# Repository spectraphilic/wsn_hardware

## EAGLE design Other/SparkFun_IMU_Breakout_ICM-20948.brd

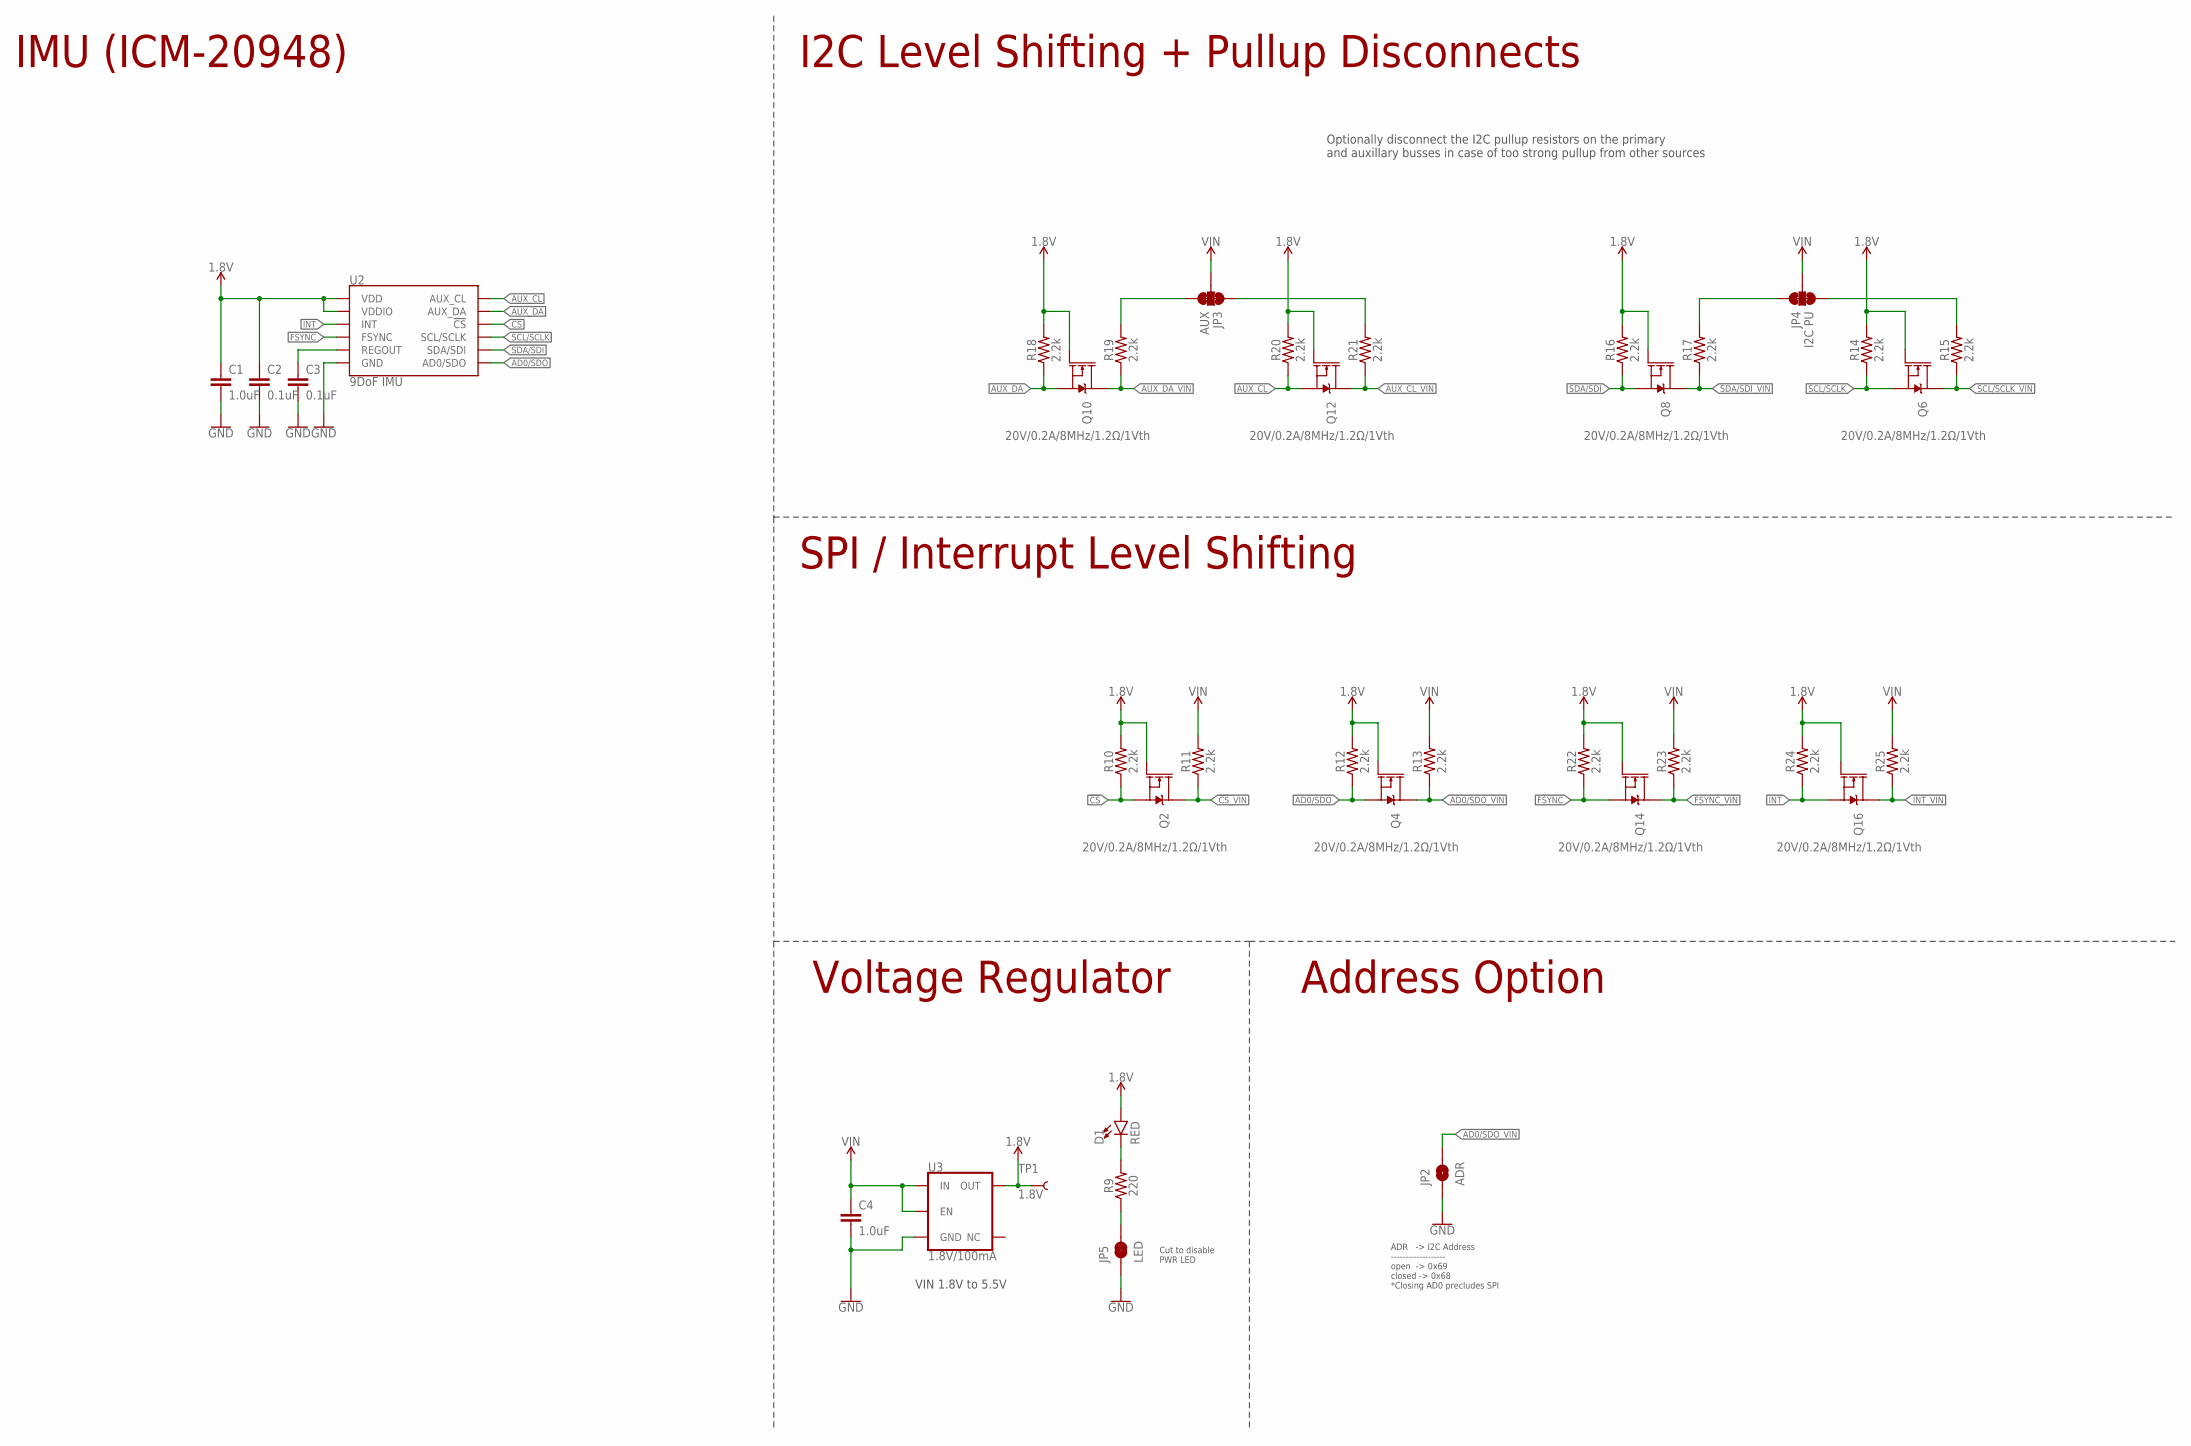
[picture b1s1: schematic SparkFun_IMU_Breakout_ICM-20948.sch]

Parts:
C1, C4: 1.0uF; 0603
C2, C3: 0.1uF; 0603
D1: RED; LED-0603
JP2: ADR; SMT-JUMPER_2_NO_SILK
JP3: AUX; SMT-JUMPER_3_2-NC_TRACE_SILK
JP4: I2C PU; SMT-JUMPER_3_2-NC_TRACE_SILK
JP5: LED; SMT-JUMPER_2_NC_TRACE_SILK
Q2, Q4, Q6, Q8, Q10, Q12, Q14, Q16: 20V/0.2A/8MHz/1.2Ω/1Vth; SOT-416FL
R9: 220; 0603
R10, R11, R12, R13, R14, R15, R16, R17, R18, R19, R20, R21, R22, R23, R24, R25: 2.2k; 0402-TIGHT
TP1: 1.8V; PAD.03X.03
U2: 9DoF IMU; QFN24-3X3
U3: 1.8V/100mA; SC70

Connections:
1.8V: C1.1, C2.1, D1.A, Q2.1 (G), Q4.1 (G), Q6.1 (G), Q8.1 (G), Q10.1 (G), Q12.1 (G), Q14.1 (G), Q16.1 (G), R10.2, R12.2, R14.2, R16.2, R18.2, R20.2, R22.2, R24.2, TP1.P$1, U2.8 (VDDIO), U2.13 (VDD), U3.5 (OUT)
!CS: Q2.2 (S), R10.1, U2.22 (!CS)
!CS!_VIN: Q2.3 (D), R11.1
AD0/SDO: Q4.2 (S), R12.1, U2.9 (AD0/SDO)
AD0/SDO_VIN: JP2.2, Q4.3 (D), R13.1
AUX_CL: Q12.2 (S), R20.1, U2.7 (AUX_CL)
AUX_CL_VIN: Q12.3 (D), R21.1
AUX_DA: Q10.2 (S), R18.1, U2.21 (AUX_DA)
AUX_DA_VIN: Q10.3 (D), R19.1
FSYNC: Q14.2 (S), R22.1, U2.11 (FSYNC)
FSYNC_VIN: Q14.3 (D), R23.1
GND: C1.2, C2.2, C3.2, C4.2, JP2.1, JP5.1, U2.18 (GND), U2.20 (GND), U3.2 (GND)
INT: Q16.2 (S), R24.1, U2.12 (INT)
INT_VIN: Q16.3 (D), R25.1
unnamed: C3.1, U2.10 (REGOUT)
unnamed: JP4.3, R15.2
unnamed: JP4.1, R17.2
unnamed: JP3.1, R21.2
unnamed: JP3.3, R19.2
unnamed: D1.C, R9.2
unnamed: JP5.2, R9.1
SCL/SCLK: Q6.2 (S), R14.1, U2.23 (SCL/SCLK)
SCL/SCLK_VIN: Q6.3 (D), R15.1
SDA/SDI: Q8.2 (S), R16.1, U2.24 (SDA/SDI)
SDA/SDI_VIN: Q8.3 (D), R17.1
VIN: C4.1, JP3.2, JP4.2, R11.2, R13.2, R23.2, R25.2, U3.1 (IN), U3.3 (EN)

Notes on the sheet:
VIN 1.8V to 5.5V
IMU (ICM-20948)
I2C Level Shifting + Pullup Disconnects
Voltage Regulator
SPI / Interrupt Level Shifting
ADR -> I2C Address ------------------- open -> 0x69 closed -> 0x68 *Closing AD0 precludes SPI
Optionally disconnect the I2C pullup resistors on the primary and auxillary busses in case of too strong pullup from other sources
Cut to disable PWR LED
Address Option

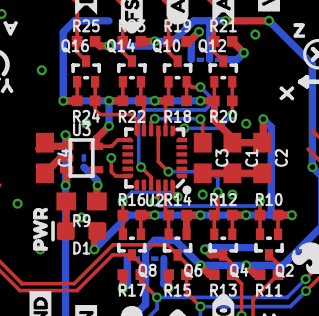
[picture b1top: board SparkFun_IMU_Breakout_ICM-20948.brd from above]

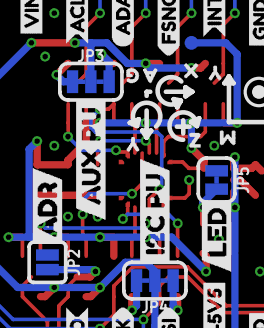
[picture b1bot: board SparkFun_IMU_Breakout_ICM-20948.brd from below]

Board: 2 copper layers, 80 parts (30 on the bottom side), 26 nets.

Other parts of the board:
U$1, U$2, U$22: GND4
U$3: PWR0
U$4, U$21: INT3
U$5, U$20: FSNC2
U$6, U$19: ACL1
U$7, U$18: ADA0
U$8: MISO13
U$9: MOSI14
U$10: SCLK15
U$11: #CS16
U$12: 1V8#5V57
U$13, U$30, U$44: VIN5
U$14: NC17
U$15: CL4
U$16: DA2
U$17: AD012
U$23: ADR2
U$25: I2C_PU21
U$27: AUX_PU24
U$28: SFE_LOGO_FLAME_.1
U$29: LED23
U$35, U$51, U$58: Y1
U$37, U$60: G5
U$38, U$61: A4
U$40, U$50, U$57: X0
U$42, U$59: Z2
U$43: QWIIC_9DOF_IMU_0
U$49: M3

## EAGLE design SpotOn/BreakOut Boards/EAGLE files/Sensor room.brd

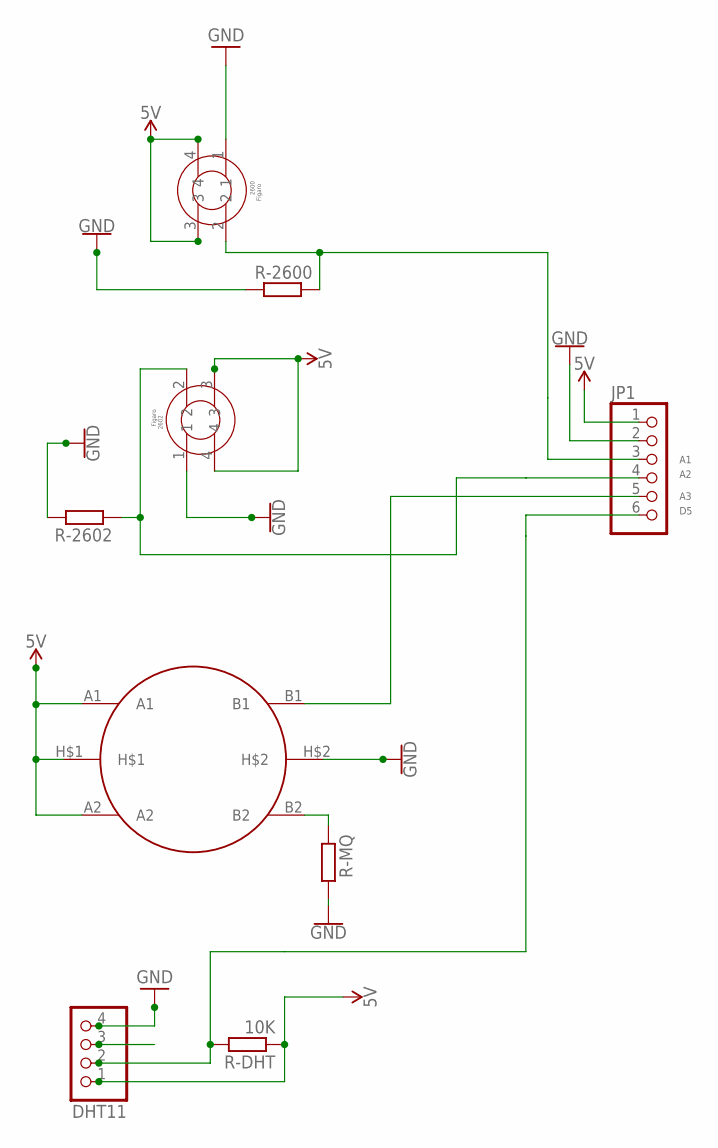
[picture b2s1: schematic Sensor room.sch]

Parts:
2600, 2602: FIGARO2602
DHT11: PINHD-1X4; 1X04
JP1: PINHD-1X6CB; 1X06-CLEANBIG
MQ-135: MQ_135_A; MQ-135
R-2600, R-2602: R0207/10; 0207/10
R-DHT: 10K; 0207/10
R-MQ: R0207/10; 0207/10

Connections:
5V: 2600.3 (4), 2600.4 (3), 2602.3 (4), 2602.4 (3), DHT11.1, JP1.1, MQ-135.A1, MQ-135.A2, MQ-135.H$1, R-DHT.1
GND: 2600.1 (2), 2602.1 (2), DHT11.4, JP1.2, MQ-135.H$2, R-2600.1, R-2602.2, R-MQ.2
unnamed: DHT11.2, JP1.6, R-DHT.2
unnamed: JP1.5, MQ-135.B1
unnamed: MQ-135.B2, R-MQ.1
unnamed: 2602.2 (1), JP1.4, R-2602.1
unnamed: 2600.2 (1), JP1.3, R-2600.2

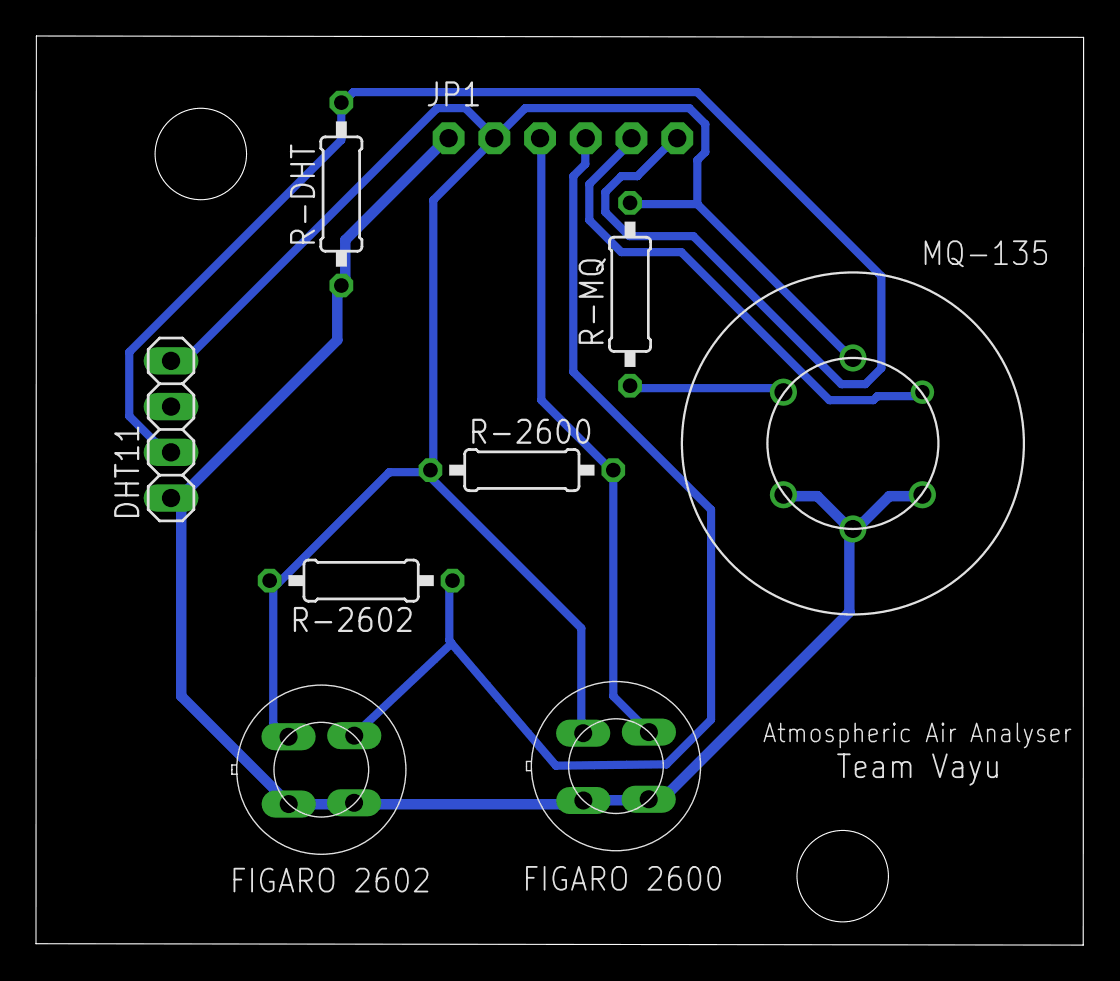
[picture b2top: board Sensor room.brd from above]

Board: 2 copper layers, 58.2 x 50.5 mm, 9 parts (0 on the bottom side), 7 nets.

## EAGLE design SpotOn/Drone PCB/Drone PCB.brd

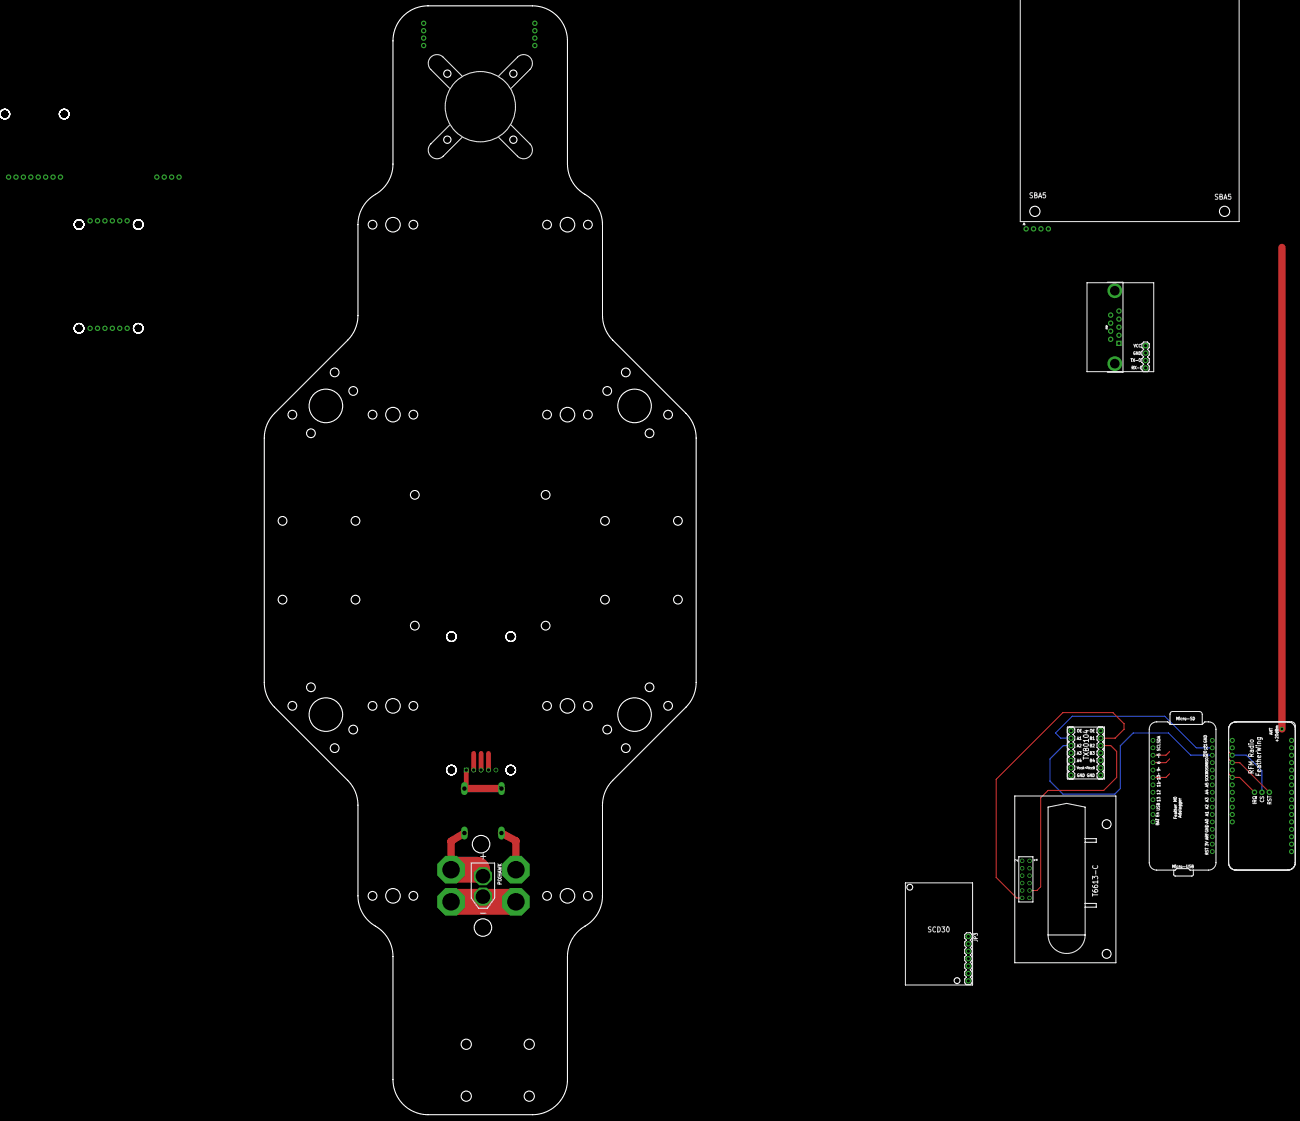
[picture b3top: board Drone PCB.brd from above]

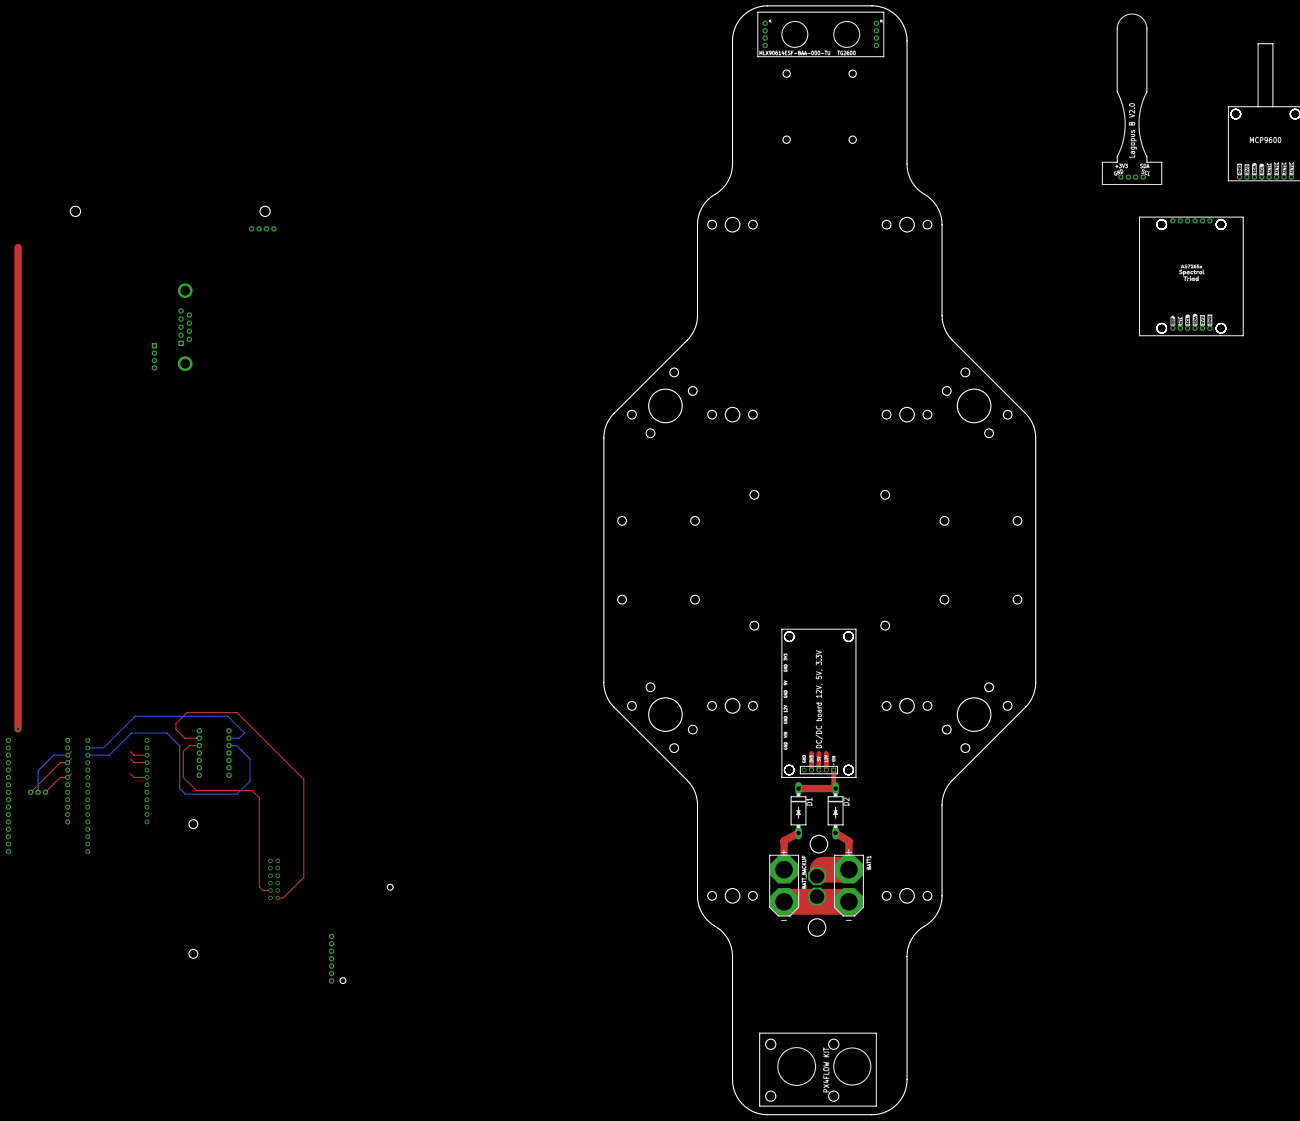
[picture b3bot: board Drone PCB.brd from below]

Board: 2 copper layers, 148.0 x 380.0 mm, 52 parts (40 on the bottom side), 27 nets.

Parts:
BATT1: XT90
BATT_BACKUP: XT90
D1, D2: P2-15
H5, H6, H7, H8: STAND-OFF
J1, J3, J7: 1X04_NO_SILK
J2: PTH; 1X04_NO_SILK
J4, J6, J10: PTH; 1X04_NO_SILK@1
J5: 61300511121
J11: 1X02_NO_SILK
J12: Serial Interface; 1X06_NO_SILK
JP1, JP2, JP7, JP10, JP11, JP12: STAND-OFF
JP3, JP5, JP6: 1X07
JP8: 1X16_ROUND
JP9: 1X12_ROUND
JP13: DB9
JP14: 1X03_ROUND_76
JP15: 1X04@1
MS2: FEATHERWING_NOHOLES
PIXHAWK: XT60
U$3: AS7265X0
U$5: SPECTRAL1
U$6: TRIAD2
U$7: GND-04
U$8: 3V3-04
U$9: GND0
U$10: 3V31
U$11: SDA2
U$12: SCL3
U$13: #ALT14
U$14: #ALT25
U$15: #ALT36
U$16: #ALT47
U$17: SDA-[)
U$18: SCL-[)
U$19: INT#-[<-04
U$20: RST#-[>-04
X2: TSW-106-07-G-D; TSW-106-XX-G-D

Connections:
3.3V: J2.2, J6.2, MS2.2
3V3: J4.2, J5.4, J10.2, JP5.2, JP15.1
5V: J3.1, J3.2, J5.3, JP6.2, X2.2
A3: J3.3, JP5.4, JP8.9
A4: JP5.3, JP8.8
CS: JP9.10, JP14.2, MS2.19
EN: JP9.2, MS2.27
F: MS2.10, MS2.23
GND: BATT1.-, BATT_BACKUP.-, J2.1, J3.4, J4.1, J5.5, J6.1, J10.1, JP5.1, JP6.1, JP8.1, JP8.13, JP13.5, JP15.2, MS2.4, PIXHAWK.-, X2.1, X2.4, X2.11
GND2: JP3.1, JP3.6
IRQ: JP9.7, JP14.1, MS2.22
MISO: JP8.4, MS2.13
MOSI: JP8.5, MS2.12
unnamed: BATT_BACKUP.+, D1.A
NC: MS2.16, X2.5, X2.7, X2.10
OE: JP5.7, JP6.7
RST: JP9.9, JP14.3, MS2.20
RX: JP5.5, JP8.3, JP15.4, MS2.14
RX-5V: JP6.6, X2.12
SCK: JP8.6, MS2.11
SCL: J2.4, J4.4, J6.4, J10.4, JP9.11, MS2.18, X2.6
SDA: J2.3, J4.3, J6.3, J10.3, JP9.12, MS2.17, X2.8
TX: JP5.6, JP8.2, JP15.3, MS2.15
TX-5V: JP6.5, X2.9
VBAT: JP9.1, MS2.28
VBATT: BATT1.+, D2.A, PIXHAWK.+
VIN: D1.C, D2.C, J5.1

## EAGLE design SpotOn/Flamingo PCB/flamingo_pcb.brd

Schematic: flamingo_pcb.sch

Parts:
J1: 1725698; SHDR6W90P0X254_1X6_1570X620X85
J2: ADAFRUIT_1X2-3.5MM
J3: 1725672; 1725672-4-2.54
J4, J9: CONN_041X04_NO_SILK; 1X04_NO_SILK
J5, J8: PTH; 1X04_NO_SILK
JP1, JP4, JP5, JP6, JP13, JP16: STAND-OFF
JP3: M07; 1X07
JP8: HEADER-1X16ROUND; 1X16_ROUND
JP9: HEADER-1X12; 1X12_ROUND
JP10: I2C_STANDARD_NO_SILK; 1X04_NO_SILK
JP11: HEADER-1X376MIL; 1X03_ROUND_76
JP12: M06NO_SILK_FEMALE_PTH; 1X06_NO_SILK
JP14: DB9
JP15: M04PTH; 1X04@1
MS2: FEATHERWING_NOHOLES
STANDOFF1: STAND-OFF

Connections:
3V3: J1.2, J5.2, J8.2, JP3.7, JP8.15, JP10.2, JP15.1, MS2.2 (3V)
5V: J1.3, J4.1, J4.2
12V: J1.4, J3.4
!ALT1: J9.1
!ALT2: J9.2
!ALT3: J9.3
!ALT4: J9.4
!RESET: JP8.16, MS2.1 (!RESET)
A0: JP8.12
A1: JP8.11
A2: JP8.10
A3: J4.3, JP8.9
A4: JP8.8
A5: JP8.7
AREF: JP8.14
C: MS2.21 (GPIO9)
CS: JP9.7, JP11.2, MS2.19 (GPIO5)
D5: JP9.10
D9: JP9.8
D12: JP9.5
D13: JP9.4
E: MS2.23 (GPIO11)
EN: JP9.2
F: MS2.10 (GPIOA5)
G: MS2.24 (GPIO12)
GND: J1.1, J2.2, J3.3, J4.4, J5.1, J8.1, JP3.1, JP3.6, JP8.1, JP8.13, JP10.1, JP12.6, JP14.5, JP15.2, MS2.4 (GND)
H: MS2.25 (GPIO13)
I: MS2.5 (GPIOA0)
IRQ: JP9.9, JP11.1, MS2.22 (GPIO10)
J: MS2.6 (GPIOA1)
K: MS2.7 (GPIOA2)
L: MS2.8 (GPIOA3)
M: MS2.9 (GPIOA4)
MAIN: J1.6, J2.1
MISO: JP8.4, MS2.13 (GPIOMISO)
MOSI: JP8.5, MS2.12 (GPIOMOSI)
NC: MS2.16 (NC)
PWM: JP3.2
RDY: JP3.3
RS-RX: J3.1, JP14.2
RS-TX: J3.2, JP14.3
RST: JP9.6, JP11.3, MS2.20 (GPIO6)
RX: JP8.3, JP15.3, MS2.14 (GPIORX)
SCK: JP8.6, MS2.11 (GPIOSCK)
SCL: J5.4, J8.4, JP3.5, JP9.11, JP10.4, MS2.18 (GPIOSCL)
SDA: J5.3, J8.3, JP3.4, JP9.12, JP10.3, MS2.17 (GPIOSDA)
TX: JP8.2, JP15.4, MS2.15 (GPIOTX)
VBAT: JP9.1
VBUS: JP9.3
VIN: J1.5

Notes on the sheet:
DC/DC board 12V, 5V, 3.3V
John Hulth
v10
Revised by:
MLX_TG2600
SCD30
Feather M0 Adalogger
RADIO FEATERWING
I2C
SPI
MCP9600 Thermocouple EMF to Temperature Converter

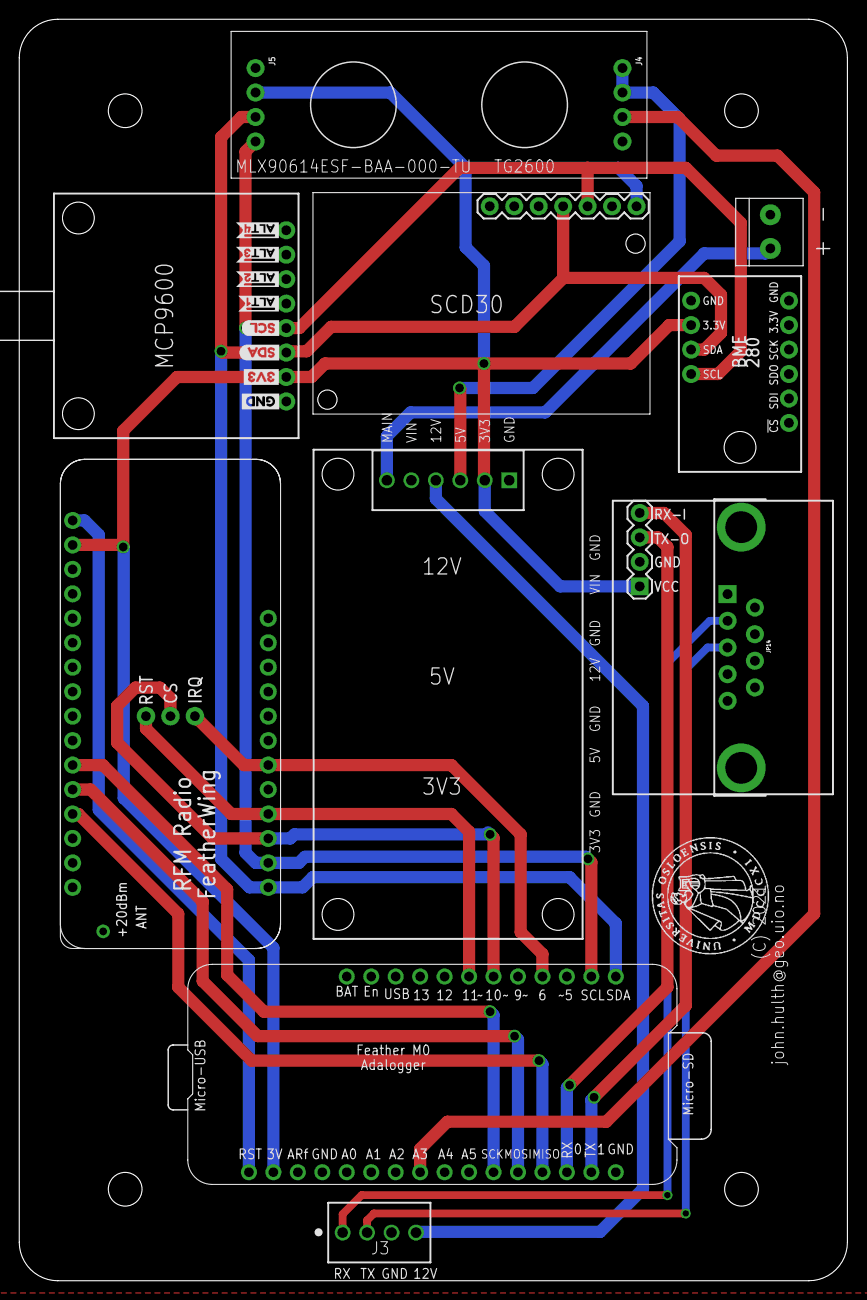
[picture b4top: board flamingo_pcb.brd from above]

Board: 2 copper layers, 86.0 x 131.0 mm, 32 parts (0 on the bottom side), 19 nets.

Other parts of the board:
U$3: UIO-LOGO-BL
U$13: GND0
U$14: 3V31
U$15: SDA2
U$16: SCL3
U$17: #ALT14
U$18: #ALT25
U$19: #ALT36
U$20: #ALT47

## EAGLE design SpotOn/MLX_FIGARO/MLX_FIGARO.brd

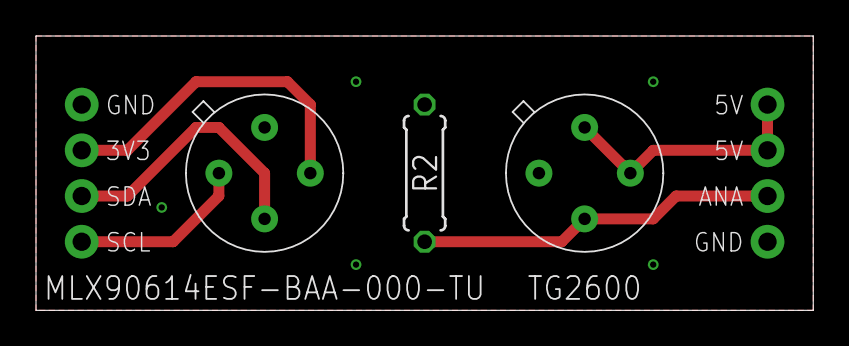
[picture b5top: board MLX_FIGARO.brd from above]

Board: 2 copper layers, 43.2 x 15.2 mm, 6 parts (1 on the bottom side), 6 nets.

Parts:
J1: 1X04_NO_SILK
J2: PTH; 1X04_NO_SILK
R2: 5k; 0207/7
U1: TG2600; TO-5
U2: MLX90614ESF-BAA-000-TU; MLX90614ESFBAA000TU
U$3: UIO-LOGO-BL

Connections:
3V3: J2.2, U2.3
5V: J1.1, J1.2, U1.3, U1.4
A3: J1.3, R2.2, U1.2
GND: J1.4, J2.1, R2.1, U1.1, U2.4
SCL: J2.4, U2.1
SDA: J2.3, U2.2

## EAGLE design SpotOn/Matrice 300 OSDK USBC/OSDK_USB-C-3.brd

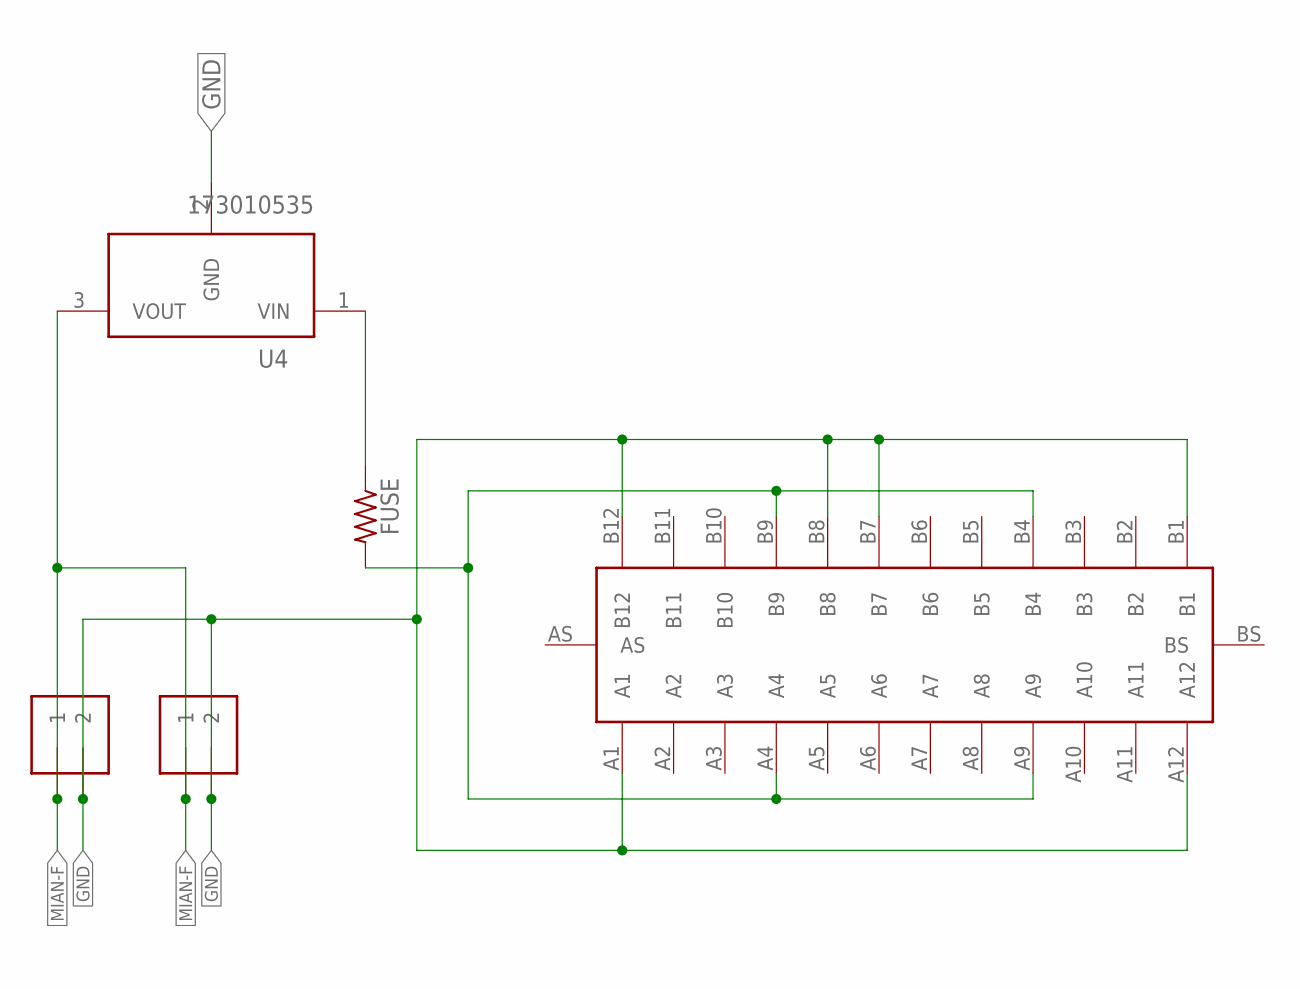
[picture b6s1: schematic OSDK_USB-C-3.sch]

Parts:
CU3124PAAHLA002-NH: USB-C
FUSE: R-US_0207/9; 0207/9
J1, J2: ADAFRUIT_1X2-3.5MM
U4: 173010535

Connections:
GND: CU3124PAAHLA002-NH.A1, CU3124PAAHLA002-NH.A12, CU3124PAAHLA002-NH.B1, CU3124PAAHLA002-NH.B7, CU3124PAAHLA002-NH.B8, CU3124PAAHLA002-NH.B12, J1.2, J2.2, U4.2 (GND)
MAIN: CU3124PAAHLA002-NH.A4, CU3124PAAHLA002-NH.A9, CU3124PAAHLA002-NH.B4, CU3124PAAHLA002-NH.B9, FUSE.2
MIAN-F: J1.1, J2.1, U4.3 (VOUT)
VIN: FUSE.1, U4.1 (VIN)

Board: 2 copper layers, 5 parts (0 on the bottom side), 4 nets, no tracks yet.

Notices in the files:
SpotOn/Flamingo PCB/flamingo_pcb.brd:
(C) 2021
parts and their libraries:
SparkFun-Connectors: Licensing: Creative Commons ShareAlike 4.0 International - https://creativecommons.org/licenses/by-sa/4.0
SparkFun-Aesthetics: Licensing: CC v3.0 Share-Alike You are welcome to use this library for commercial purposes.
